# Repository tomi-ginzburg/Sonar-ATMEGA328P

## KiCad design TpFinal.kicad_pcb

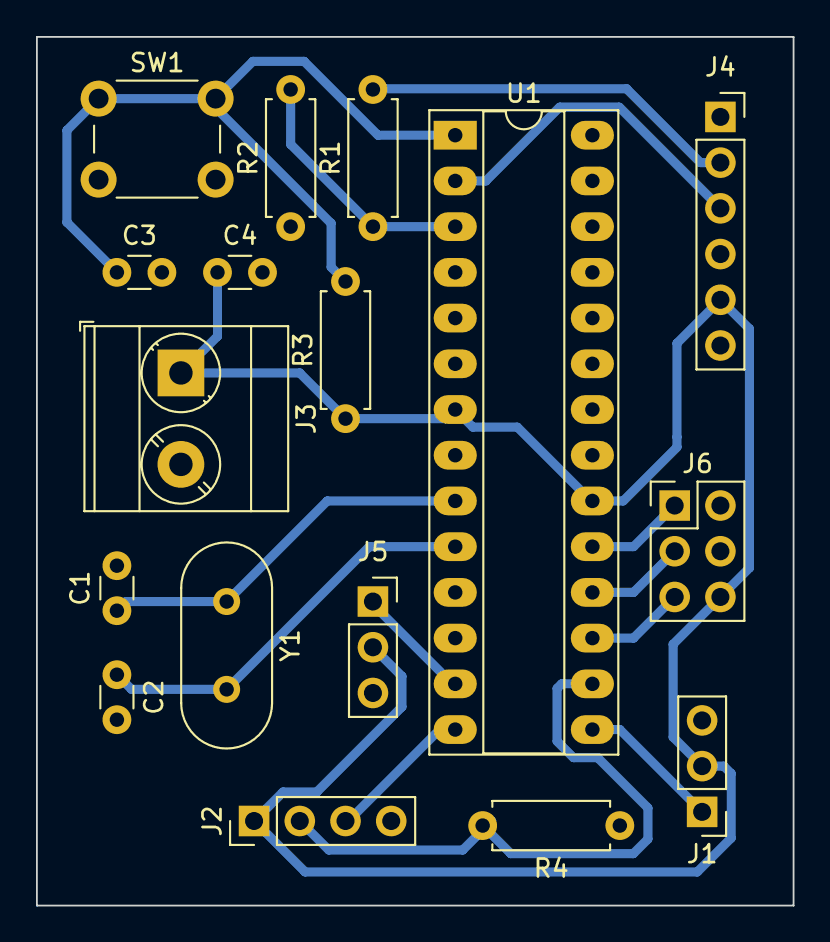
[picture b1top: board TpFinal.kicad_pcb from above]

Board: 2 copper layers, 42.0 x 48.3 mm, 17 parts (0 on the bottom side), 15 nets.

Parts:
C1, C2: 22p; C_Disc_D3.0mm_W1.6mm_P2.50mm
C3, C4: 100n; C_Disc_D3.0mm_W1.6mm_P2.50mm
J1: Servo; PinHeader_1x03_P2.54mm_Vertical
J2: UltraSonido; PinHeader_1x04_P2.54mm_Vertical
J3: Vin; TerminalBlock_Phoenix_MKDS-3-2-5.08_1x02_P5.08mm_Horizontal
J4: BT HC-05; PinSocket_1x06_P2.54mm_Vertical
J5: KY-8; PinSocket_1x03_P2.54mm_Vertical
J6: ICSP; PinHeader_2x03_P2.54mm_Vertical
R1, R4: 1k; R_Axial_DIN0207_L6.3mm_D2.5mm_P7.62mm_Horizontal
R2: 2k; R_Axial_DIN0207_L6.3mm_D2.5mm_P7.62mm_Horizontal
R3: 10k; R_Axial_DIN0207_L6.3mm_D2.5mm_P7.62mm_Horizontal
SW1: SW_Push; SW_PUSH_6mm
U1: ATmega328P-PU; DIP-28_W7.62mm_Socket_LongPads
Y1: 16Meg; Crystal_HC49-4H_Vertical

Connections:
GND: C1.2, C2.2, C3.2, C4.2, J1.3, J2.4, J3.2, J4.4, J5.3, J6.4, R2.1, R4.1, SW1.2, U1.8, U1.22
unnamed: C1.1, U1.9, Y1.1
unnamed: C2.1, U1.10, Y1.2
unnamed: C3.1, J6.2, R3.2, SW1.1, U1.1
unnamed: J1.1, U1.15
unnamed: J2.2, R4.2, U1.16
unnamed: J2.3, U1.14
unnamed: J4.2, R1.2
unnamed: J4.3, U1.2
unnamed: J5.1, U1.13
unnamed: J6.1, U1.19
unnamed: J6.3, U1.18
unnamed: J6.5, U1.17
unnamed: R1.1, R2.2, U1.3
Vcc: C4.1, J1.2, J2.1, J3.1, J4.5, J5.2, J6.6, R3.1, U1.7, U1.20
